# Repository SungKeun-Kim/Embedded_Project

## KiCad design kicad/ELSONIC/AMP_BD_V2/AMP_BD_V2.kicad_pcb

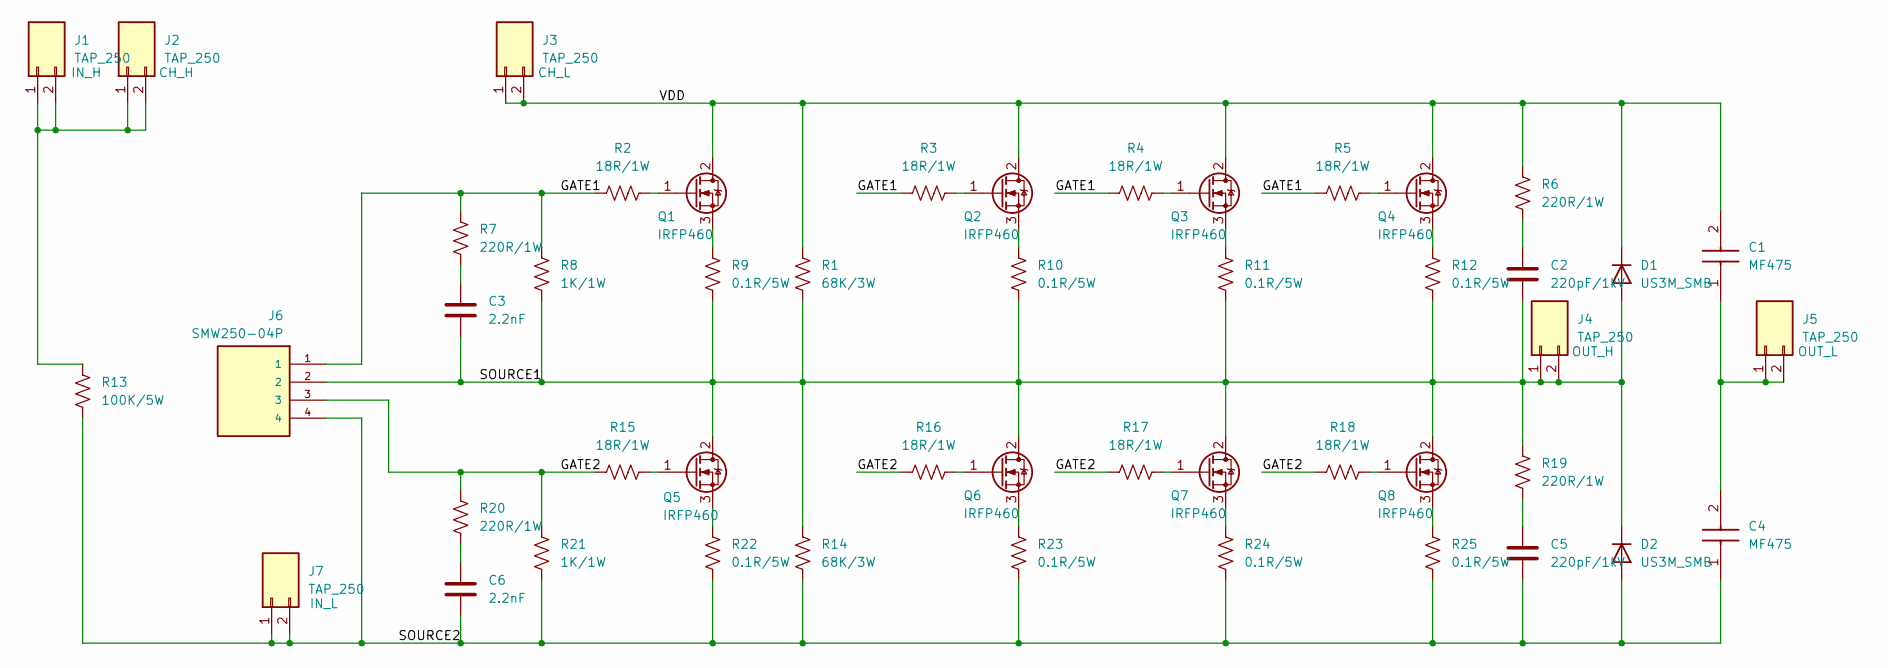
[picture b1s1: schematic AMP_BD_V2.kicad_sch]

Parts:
C1, C4: MF475
C2, C5: 220pF/1kV; C_3216Metric; LCSC C46312
C3, C6: 2.2nF; C_3216Metric; LCSC C577152
D1, D2: US3M_SMB; LCSC C908435
J1, J2, J3, J4, J5, J7: TAP_250
J6: SMW250-04P; SMW250_04P
Q1, Q2, Q3, Q4, Q5, Q6, Q7, Q8: IRFP460; TO-247-3_Vertical
R1, R14: 68K/3W; R_Axial_3W_P22mm
R2, R3, R4, R5, R15, R16, R17, R18: 18R/1W; R_6332Metric; LCSC C458686
R6, R7, R19, R20: 220R/1W; R_6332Metric; LCSC C49247113
R8, R21: 1K/1W; R_6332Metric; LCSC C310400
R9, R10, R11, R12, R22, R23, R24, R25: 0.1R/5W; R_Axial_5W_P27mm
R13: 100K/5W; R_Axial_5W_P27mm

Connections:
/GATE1: J6.1, R2.1, R3.1, R4.1, R5.1, R7.2, R8.2
/GATE2: J6.3, R15.1, R16.1, R17.1, R18.1, R20.2, R21.2
/SOURCE1: C2.2, C3.1, D1.2 (A), D2.1 (K), J4.1, J4.2, J6.2, Q5.2 (D), Q6.2 (D), Q7.2 (D), Q8.2 (D), R1.2, R8.1, R9.2, R10.2, R11.2, R12.2, R14.1, R19.2
/SOURCE2: C4.1, C5.2, C6.1, D2.2 (A), J6.4, J7.1, J7.2, R13.2, R14.2, R21.1, R22.2, R23.2, R24.2, R25.2
/VDD: C1.2, D1.1 (K), J3.1, J3.2, Q1.2 (D), Q2.2 (D), Q3.2 (D), Q4.2 (D), R1.1, R6.2
unnamed: C2.1, R6.1
unnamed: C3.2, R7.1
unnamed: C5.1, R19.1
unnamed: C6.2, R20.1
unnamed: J1.1, J1.2, J2.1, J2.2, R13.1
unnamed: C1.1, C4.2, J5.1, J5.2
unnamed: Q1.1 (G), R2.2
unnamed: Q1.3 (S), R9.1
unnamed: Q2.1 (G), R3.2
unnamed: Q2.3 (S), R10.1
unnamed: Q3.1 (G), R4.2
unnamed: Q3.3 (S), R11.1
unnamed: Q4.1 (G), R5.2
unnamed: Q4.3 (S), R12.1
unnamed: Q5.1 (G), R15.2
unnamed: Q5.3 (S), R22.1
unnamed: Q6.1 (G), R16.2
unnamed: Q6.3 (S), R23.1
unnamed: Q7.1 (G), R17.2
unnamed: Q7.3 (S), R24.1
unnamed: Q8.1 (G), R18.2
unnamed: Q8.3 (S), R25.1

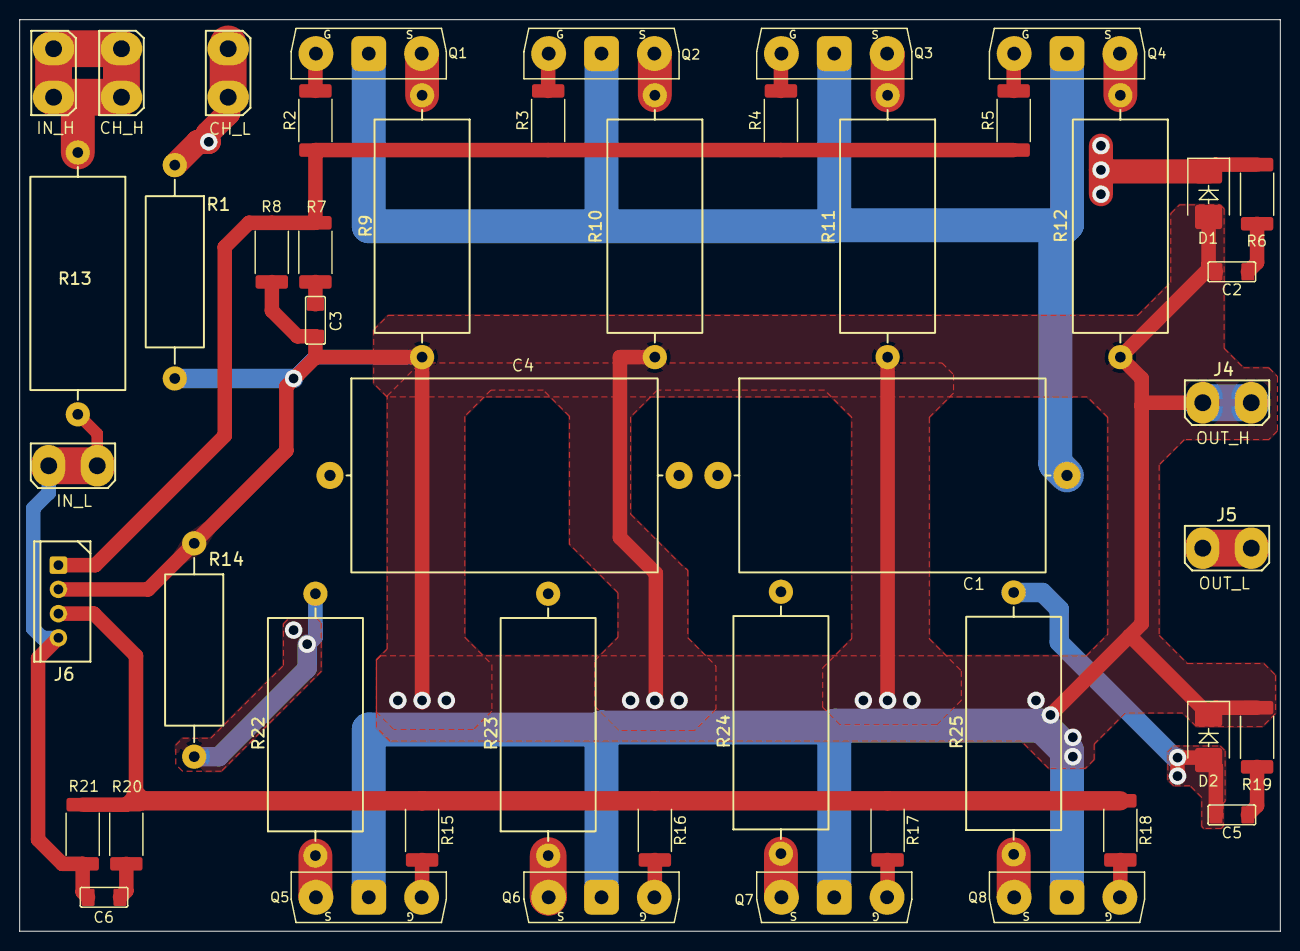
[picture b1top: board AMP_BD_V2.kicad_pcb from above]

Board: 2 copper layers, 130.0 x 94.0 mm, 48 parts (0 on the bottom side), 27 nets.

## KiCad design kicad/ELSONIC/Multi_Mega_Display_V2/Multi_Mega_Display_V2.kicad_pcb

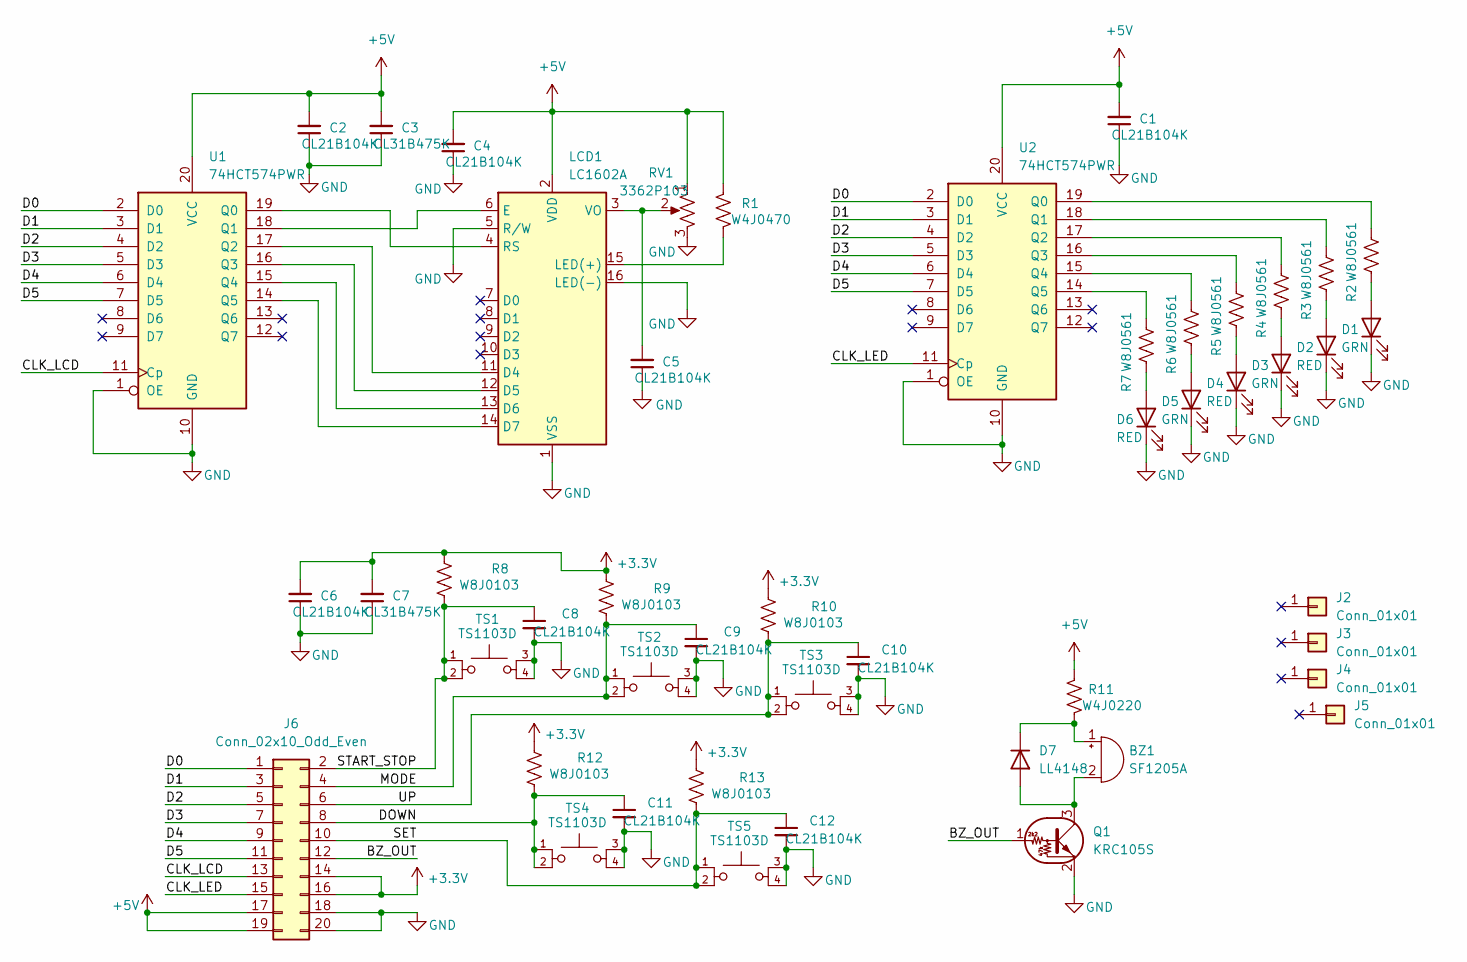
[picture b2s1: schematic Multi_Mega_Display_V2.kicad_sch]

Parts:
BZ1: SF1205A; Buzzer_12x9.5RM7.6
C1, C2, C4, C5, C6, C8, C9, C10, C11, C12: CL21B104K; C_2012Metric; LCSC C1711
C3, C7: CL31B475K; C_3216Metric; LCSC C1872
D1: GRN; LED_NORMAL
D2: RED; LED_H_LSET
D3: GRN; LED_8POWER
D4: RED; LED_REMOTE
D5: GRN; LED_EXT
D6: RED; LED_TXRX
D7: LL4148; LL4148_MELF; LCSC C68883
J2, J3, J4, J5: Conn_01x01; MTHole_3.5mm_7.5mmPad_GND
J6: Conn_02x10_Odd_Even; IDC-Header_2x10_P2.54mm_Vertical
LCD1: LC1602A
Q1: KRC105S; SOT-23_KRC105S; LCSC C112793
R1: W4J0470; R_3216Metric; LCSC C25384
R2, R3, R4, R5, R6, R7: W8J0561; R_2012Metric; LCSC C25319
R8, R9, R10, R12, R13: W8J0103; R_2012Metric; LCSC C25612
R11: W4J0220; R_3216Metric; LCSC C25364
RV1: 3362P103; TRIM_3362P
TS1, TS2, TS3, TS4, TS5: TS1103D; SW_PUSH-12mm
U1, U2: 74HCT574PWR; TSSOP-20_4.4x6.5mm_P0.65mm; LCSC C2652839

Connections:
+3.3V: C6.2, C7.2, J6.14, J6.16, R8.2, R9.2, R10.2, R12.2, R13.2
+5V: C1.2, C2.2, C3.2, C4.2, J6.17, J6.19, LCD1.2 (VDD), R1.2, R11.2, RV1.1, U1.20 (VCC), U2.20 (VCC)
/BZ_OUT: J6.12, Q1.1 (B)
/CLK_LCD: J6.13, U1.11 (Cp)
/CLK_LED: J6.15, U2.11 (Cp)
/D0: J6.1, U1.2 (D0), U2.2 (D0)
/D1: J6.3, U1.3 (D1), U2.3 (D1)
/D2: J6.5, U1.4 (D2), U2.4 (D2)
/D3: J6.7, U1.5 (D3), U2.5 (D3)
/D4: J6.9, U1.6 (D4), U2.6 (D4)
/D5: J6.11, U1.7 (D5), U2.7 (D5)
/DOWN: C11.1, J6.8, R12.1, TS4.1, TS4.2
/MODE: C9.1, J6.4, R9.1, TS2.1, TS2.2
/SET: C12.1, J6.10, R13.1, TS5.1, TS5.2
/START_STOP: C8.1, J6.2, R8.1, TS1.1, TS1.2
/UP: C10.1, J6.6, R10.1, TS3.1, TS3.2
GND: C1.1, C2.1, C3.1, C4.1, C5.1, C6.1, C7.1, C8.2, C9.2, C10.2, C11.2, C12.2, D1.1 (K), D2.1 (K), D3.1 (K), D4.1 (K), D5.1 (K), D6.1 (K), J6.18, J6.20, LCD1.1 (VSS), LCD1.5 (R/W), LCD1.16 (LED(-)), Q1.2 (E), RV1.3, TS1.3, TS1.4, TS2.3, TS2.4, TS3.3, TS3.4, TS4.3, TS4.4, TS5.3, TS5.4, U1.1 (OE), U1.10 (GND), U2.1 (OE), U2.10 (GND)
unnamed: BZ1.1 (+), D7.1 (K), R11.1
unnamed: BZ1.2 (-), D7.2 (A), Q1.3 (C)
unnamed: D1.2 (A), R2.1
unnamed: D2.2 (A), R3.1
unnamed: D3.2 (A), R4.1
unnamed: D4.2 (A), R5.1
unnamed: D5.2 (A), R6.1
unnamed: D6.2 (A), R7.1
unnamed: LCD1.11 (D4), U1.17 (Q2)
unnamed: LCD1.12 (D5), U1.16 (Q3)
unnamed: LCD1.13 (D6), U1.15 (Q4)
unnamed: LCD1.14 (D7), U1.14 (Q5)
unnamed: LCD1.6 (E), U1.18 (Q1)
unnamed: LCD1.15 (LED(+)), R1.1
unnamed: LCD1.4 (RS), U1.19 (Q0)
unnamed: C5.2, LCD1.3 (VO), RV1.2
unnamed: R2.2, U2.19 (Q0)
unnamed: R3.2, U2.18 (Q1)
unnamed: R4.2, U2.17 (Q2)
unnamed: R5.2, U2.16 (Q3)
unnamed: R6.2, U2.15 (Q4)
unnamed: R7.2, U2.14 (Q5)

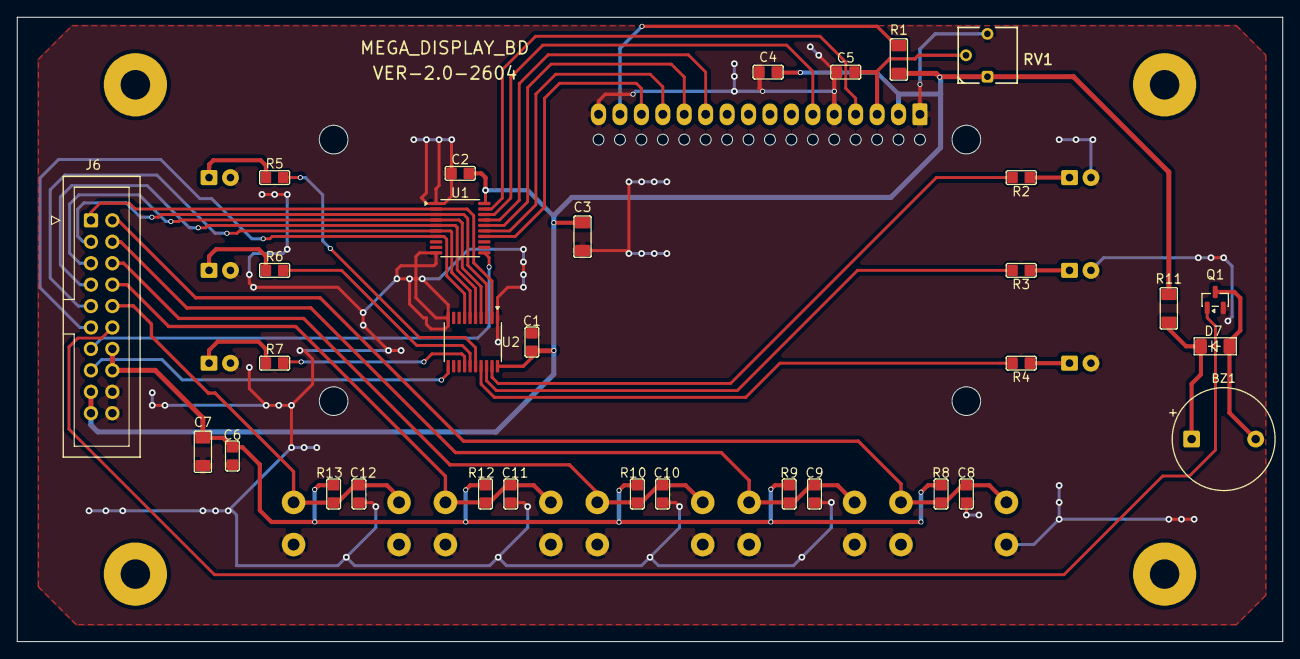
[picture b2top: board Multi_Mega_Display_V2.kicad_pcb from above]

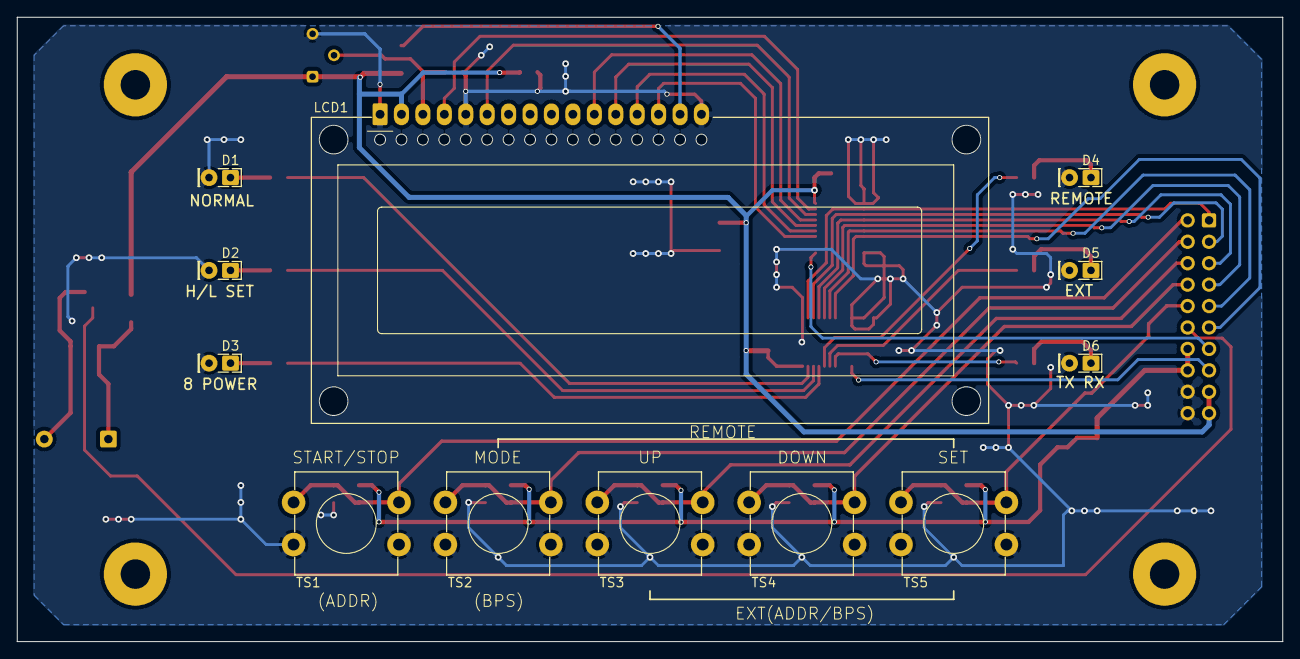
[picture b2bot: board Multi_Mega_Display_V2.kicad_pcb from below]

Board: 2 copper layers, 150.0 x 74.0 mm, 48 parts (12 on the bottom side), 39 nets.

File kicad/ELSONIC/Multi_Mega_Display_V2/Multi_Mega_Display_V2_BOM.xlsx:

Comment | Designator | Footprint | LCSC
74HCT574PWR | U1,U2 | TSSOP-20_4.4x6.5mm_P0.65mm | C2652839
LL4148 | D7 | LL4148_MELF | C68883
KRC105S | Q1 | SOT-23_KRC105S | C112793
CL21B104K | C1,C2,C4,C5,C6,C8,C9,C10,C11,C12 | C_2012Metric | C1711
CL31B475K | C3,C7 | C_3216Metric | C1872
W8J0561 | R2,R3,R4,R5,R6,R7 | R_2012Metric | C25319
W8J0103 | R8,R9,R10,R12,R13 | R_2012Metric | C25612
W4J0470 | R1 | R_3216Metric | C25384
W4J0220 | R11 | R_3216Metric | C25364

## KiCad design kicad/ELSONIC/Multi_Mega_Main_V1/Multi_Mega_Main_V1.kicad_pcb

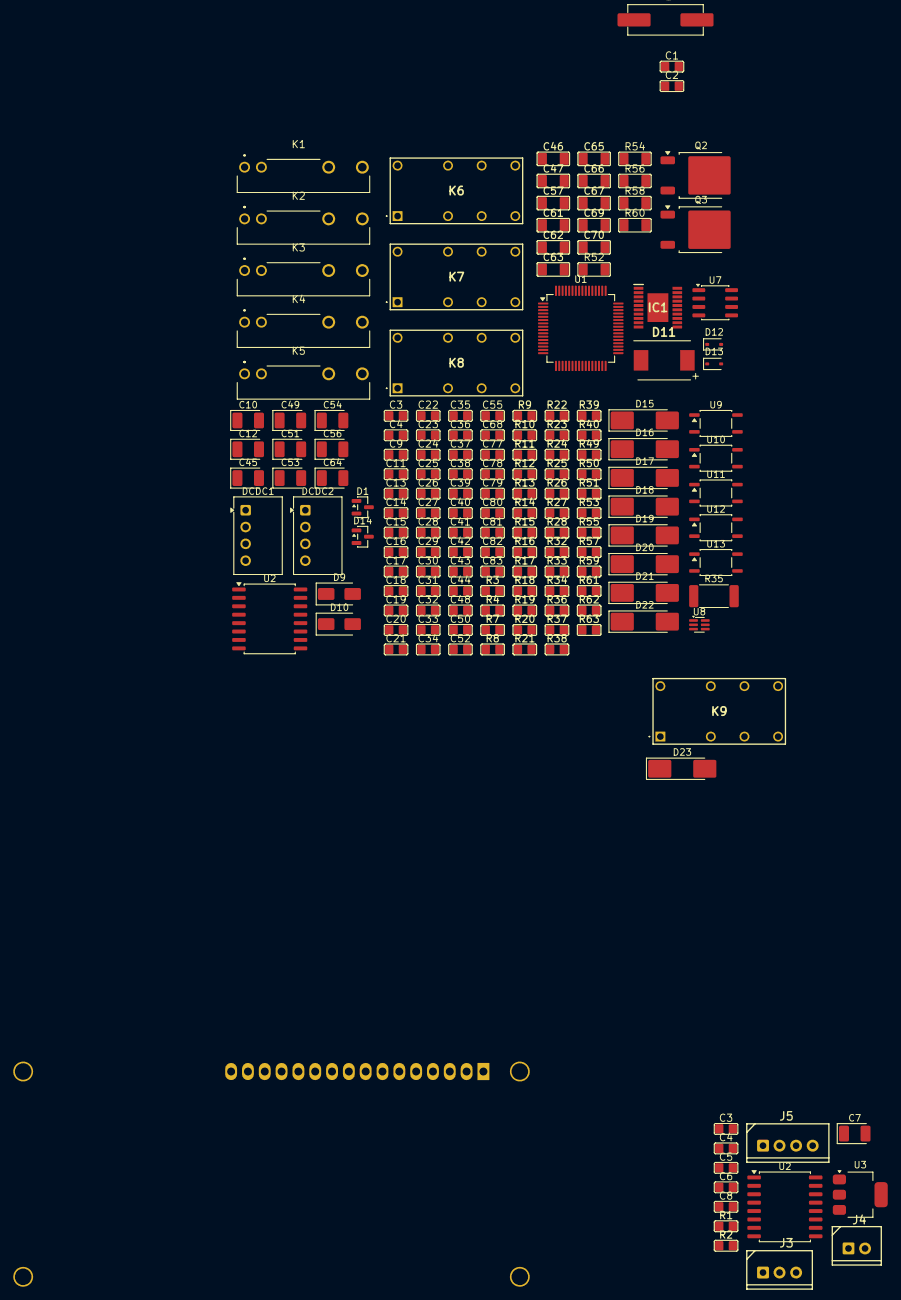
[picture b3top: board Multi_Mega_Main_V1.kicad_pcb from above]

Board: 2 copper layers, 172 parts (1 on the bottom side), 83 nets, no tracks yet.

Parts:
C1, C2: CG330J; C_2012Metric
C3, C5, C6, C9, C11, C13, C15, C16, C18, C19, C20, C22, C23, C24, C25, C26, C27, C29, C31, C32, C34, C37, C38, C39, C40, C41, C44, C48, C50, C55, C68, C81, C83: CL104K; C_2012Metric
C3#2, C4, C42, C43: CG220J; C_2012Metric
C4#2, C14, C30: CL475K; C_2012Metric
C7, C45, C56: TAJB106K; CP_EIA-3528-21_Kemet-B_HandSolder
C8, C28, C80, C82: CL106K; C_2012Metric
C10, C49: 47UF50V; CP_EIA-3528-21_Kemet-B_HandSolder
C12, C51: 10UF25V; CP_EIA-3528-21_Kemet-B_HandSolder
C17, C33: CL105K; C_2012Metric
C21: CG101J; C_2012Metric
C35, C36, C77, C78, C79: B472K; C_2012Metric
C46, C47: 225J100V; C_3216Metric
C52: 104KC100V; C_2012Metric
C53: 10UF100V; CP_EIA-3528-21_Kemet-B_HandSolder
C54: 1000UF63V; CP_EIA-3528-21_Kemet-B_HandSolder
C57: 105J100V; C_3216Metric
C61: 102J100V; C_3216Metric
C62: 223J100V; C_3216Metric
C63, C65: 330J100V; C_3216Metric
C64: 220UF50V; CP_EIA-3528-21_Kemet-B_HandSolder
C66, C69: 103J100V; C_3216Metric
C67: 226J50V; C_3216Metric
C70: 101J100V; C_3216Metric
D1: BAV99; SOT-23
D9, D10: SS24; D_SMA
D11: B3100-13-F; B3100_13_F
D12, D13: BAT54WS; D_SOD-323
D14: SM712_SOT23; SOT-23
D15, D16, D17, D18, D19, D20, D21, D22, D23: LL4148; D_MELF_Hand
DCDC1, DCDC2: MUS2415N; Converter_DCDC_TRACO_TME_24xxS_Single_THT
IC1: LM5005MHX_NOPB; SOP65P640X110-21N
J3: SMW250-03P; SMW250_03P
J4: SMW250-02P; SMW250_02P
J5: SMW250-04P; SMW250_04P
K1, K2, K3, K4, K5: PA1A_5V; PA1A5V
K6, K7, K8, K9: G6A274; G6A274PST15USDC12
LCD1: LC1602A; WC1602A
Q2, Q3: STD25N10F7; TO-252-2
R1, R2: FR-0747RL; R_2012Metric
R3, R7, R14, R15, R16, R17, R18, R20, R53, R55, R57, R59, R61, R63: W8-J0103; R_2012Metric
R4: W4-J0470; R_2012Metric
R8, R9, R10, R11, R12, R13: W8-J0561; R_2012Metric
R19: W4-J0220; R_2012Metric
R21: W8-J0104; R_2012Metric
R22, R25: W4-J0103; R_2012Metric
R23, R24: 1W-4.7; R_2012Metric
R26: W4-J0334; R_2012Metric
R27: W4-F4992; R_2012Metric
R28: W4-J0333; R_2012Metric
R32, R39: W4-F1102; R_2012Metric
R33, R40: W4-F1501; R_2012Metric
R34: W4-F2701; R_2012Metric
R35: 1W-F100; R_2512_6332Metric_Pad1.40x3.35mm_HandSolder
R36: W4-J0100; R_2012Metric
R37: W4-J0123; R_2012Metric
R38: W4-J0223; R_2012Metric
R49, R50: W8-J0431; R_2012Metric
R51: W4-J0121; R_2012Metric
R52, R54, R56, R58, R60: W4-J0472; R_3216Metric
R62: FR-0733RL; R_2012Metric
U1: STM32G474RBT6; LQFP-64_10x10mm_P0.5mm
U2, U2#2: UCC21520DW; SOIC-16W_7.5x10.3mm_P1.27mm
U3: AMS1117-3.3; SOT-223-3_TabPin2
U7: MAX3485; SOIC-8_3.9x4.9mm_P1.27mm
U8: INA190A4; SOT-363_SC-70-6
U9, U10, U11, U12, U13: TLP185; SOIC-4_4.55x3.7mm_P2.54mm
Y1: HC-49SMD; Crystal_SMD_HC49-SD

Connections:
+3.3V: C3.2, C4#2.2, C5.2, C7.1, C16.2, C17.2, C19.2, C22.2, C23.2, C24.2, C25.2, C26.2, C55.2, C56.1, C68.2, D1.2 (A), J5.3, R3.2, R7.2, R14.2, R15.2, R16.2, R17.2, R18.2, R49.2, R53.2, R55.2, R57.2, R59.2, R61.2, U1.1 (VBAT), U1.16 (VDD), U1.32 (VDD), U1.48 (VDD), U1.64 (VDD), U2.3 (VCCI), U2.8 (VCCI), U3.2 (VO), U7.8 (VCC), U8.3 (V+)
+5V: C6.2, C8.2, C13.2, C14.2, C15.2, C31.2, C44.2, C45.1, C80.2, C81.2, C82.2, C83.2, D15.1 (K), D16.1 (K), D17.1 (K), D18.1 (K), D19.1 (K), D20.1 (K), D21.1 (K), D22.1 (K), D23.1 (K), J5.1, K1.2 (++), K2.2 (++), K3.2 (++), K4.2 (++), K5.2 (++), K6.1 (COIL+), K7.1 (COIL+), K8.1 (COIL+), K9.1 (COIL+), LCD1.2 (VDD), R4.2, R19.2, U3.3 (VI)
+15VA: C11.2, C12.1, DCDC1.4 (+Vout), U2.16 (VDDA)
+15VB: C50.2, C51.1, DCDC2.4 (+Vout), Q2.3 (S), Q3.2 (D), R22.1, U2.11 (VDDB)
+24V: C9.2, C10.1, C33.2, C34.2, C48.2, C49.1, DCDC1.2 (+Vin), DCDC2.2 (+Vin), R52.2, R54.2, R56.2, R58.2, R60.2
+48V: C46.2, C47.2, C52.2, C53.1, C54.1, IC1.3 (VIN_1), IC1.4 (VIN_2), R26.1
+VBUS: Q2.2 (D), R35.1, U8.5 (-)
/ADC1_IN1: D12.1 (K), U1.12 (PA0)
/ADC1_IN2: D13.1 (K), U1.13 (PA1)
/ADC2_IN3: U1.20 (PA6), U8.6
/ADC2_IN4: R39.1, R40.2, U1.21 (PA7)
/BCD_BIT1_M: C36.2, R55.1, U1.52 (PC10), U10.6
/BCD_BIT2_M: C77.2, R57.1, U1.53 (PC11), U11.6
/BCD_BIT3_M: C78.2, R59.1, U1.54 (PC12), U12.6
/CHA1: R1.1, U1.42 (PA8)
/CHA2: R2.1, U1.43 (PA9)
/DAC1_OUT1: R34.2, U1.18 (PA4)
/DE_RS485: U1.24 (PB0), U7.3 (DE)
/DOWN: C40.1, R17.1, U1.11 (PC3)
/INA: C3#2.2, C42.2, J4.1, R1.2, U2.1 (INA), U2#2.1 (INA)
/INB: C4.2, C43.2, J4.2, R2.2, U2.2 (INB), U2#2.2 (INB)
/LC_RELAY_IN: K6.4 (COM1), K6.13 (COM2)
/LC_RELAY_OUT: K9.6 (NC1), K9.11 (NC2)
/MODE: C38.1, R14.1, U1.9 (PC1)
/NRST: C18.2, C20.1, D1.3 (K), R3.1, U1.7 (PG10)
/REMOTE_M: C35.2, R53.1, U1.51 (PA15), U9.6
/SENSOR_M: C79.2, R61.1, U1.55 (PD2), U13.6
/SET: C41.1, R18.1, U1.22 (PC4)
/START_STOP: C37.1, R15.1, U1.8 (PC0)
/SWDIO: C21.2, R7.1, U1.49 (PA13)
/UP: C39.1, R16.1, U1.10 (PC2)
/USART2_RX: U1.17 (PA3), U7.1 (RO)
/USART2_TX: U1.14 (PA2), U7.4 (DI)
//RE_RS485: U1.25 (PB1), U7.2 (~RE)
GND: C1.1, C2.1, C3.1, C3#2.1, C4.1, C4#2.1, C5.1, C6.1, C7.2, C8.1, C9.1, C10.2, C13.1, C14.1, C15.1, C16.1, C17.1, C18.1, C19.1, C21.1, C22.1, C23.1, C24.1, C25.1, C26.1, C27.1, C28.1, C29.1, C30.1, C31.1, C32.1, C33.1, C34.1, C35.1, C36.1, C37.2, C38.2, C39.2, C40.2, C41.2, C42.1, C43.1, C44.1, C45.2, C48.1, C49.2, C55.1, C56.2, C77.1, C78.1, C79.1, C80.1, C81.1, C82.1, C83.1, D1.1 (K), DCDC1.1 (-Vin), DCDC2.1 (-Vin), J3.3, J5.2, J5.4, LCD1.1 (VSS), LCD1.5 (R/W), LCD1.16 (LED(-)), R20.1, R21.1, R50.1, R63.1, U1.15 (VSS), U1.27 (VSSA), U1.31 (VSS), U1.47 (VSS), U1.63 (VSS), U2.4 (GND), U3.1 (GND), U7.5 (GND), U9.4, U10.4, U11.4, U12.4, U13.4
GNDA: C11.1, C12.2, DCDC1.3 (-Vout), U2.14 (VSSA)
GNDB: C46.1, C47.1, C50.1, C51.2, C52.1, C53.2, C54.2, C57.1, C61.1, C64.2, C65.1, C67.1, C68.1, C69.1, C70.1, DCDC2.3 (-Vout), IC1.10 (AGND), IC1.13 (PGND_1), IC1.14 (PGND_2), Q3.3 (S), R25.1, R28.1, R33.1, R36.1, R37.2, R40.1, U2.9 (VSSB), U8.1 (REF), U8.2 (GND)
unnamed: C63.1, R36.2
unnamed: C66.2, R27.1
unnamed: D9.2 (A), Q2.1 (G), R22.2, R23.1
unnamed: D9.1 (K), R23.2, U2.15 (OUTA)
unnamed: D10.2 (A), Q3.1 (G), R24.1, R25.2
unnamed: D10.1 (K), R24.2, U2.10 (OUTB)
unnamed: D11.2 (A), IC1.15 (IS_1), IC1.16 (IS_2)
unnamed: C62.1, C63.2, D11.1 (K), IC1.17 (SW_1), IC1.18 (SW_2), IC1.19 (PRE)
unnamed: D14.1 (A1), D14.2 (A2), R49.1, U7.6 (A)
unnamed: D14.3 (common), R50.2, U7.7 (B)
unnamed: D15.2 (A), K1.1 (-)
unnamed: D16.2 (A), K2.1 (-)
unnamed: D17.2 (A), K3.1 (-)
unnamed: D18.2 (A), K4.1 (-)
unnamed: D19.2 (A), K5.1 (-)
unnamed: D20.2 (A), K6.16 (COIL-)
unnamed: D21.2 (A), K7.16 (COIL-)
unnamed: D22.2 (A), K8.16 (COIL-)
unnamed: D23.2 (A), K9.16 (COIL-)
unnamed: C62.2, IC1.20 (BST)
unnamed: C70.2, IC1.6 (COMP), R27.2, R38.2
unnamed: C66.1, C69.2, IC1.7 (FB), R32.1, R33.2, R34.1, R38.1
unnamed: C64.1, C67.2, IC1.12 (OUT), R32.2, R35.2, R39.2, U8.4 (+)
unnamed: C65.2, IC1.9 (RAMP)
unnamed: IC1.8 (RT), R28.2
unnamed: IC1.2 (SD), R26.2, R37.1
unnamed: C61.2, IC1.11 (SS)
unnamed: C57.2, IC1.1 (VCC)
unnamed: R63.2, U1.61 (PB8)
unnamed: K6.6 (NC1), K6.11 (NC2), K7.4 (COM1), K7.13 (COM2)
unnamed: K7.6 (NC1), K7.11 (NC2), K8.4 (COM1), K8.13 (COM2)
unnamed: K8.6 (NC1), K8.11 (NC2), K9.4 (COM1), K9.13 (COM2)
unnamed: LCD1.15 (LED(+)), R4.1
unnamed: C32.2, LCD1.3 (VO)
unnamed: R52.1, U9.1
unnamed: R54.1, U10.1
unnamed: R56.1, U11.1
unnamed: R58.1, U12.1
unnamed: R60.1, U13.1
unnamed: R62.1, U1.59 (PB6)
unnamed: C1.2, U1.5 (PF0), Y1.2
unnamed: C2.2, U1.6 (PF1), Y1.1
unnamed: C27.2, C28.2, C29.2, C30.2, U1.28 (VREF+), U1.29 (VDDA)
unnamed: R20.2, U2.5 (DIS)
unnamed: R21.2, U2.6 (DT)
unnamed: U2#2.3 (VCCI), U2#2.8 (VCCI)
